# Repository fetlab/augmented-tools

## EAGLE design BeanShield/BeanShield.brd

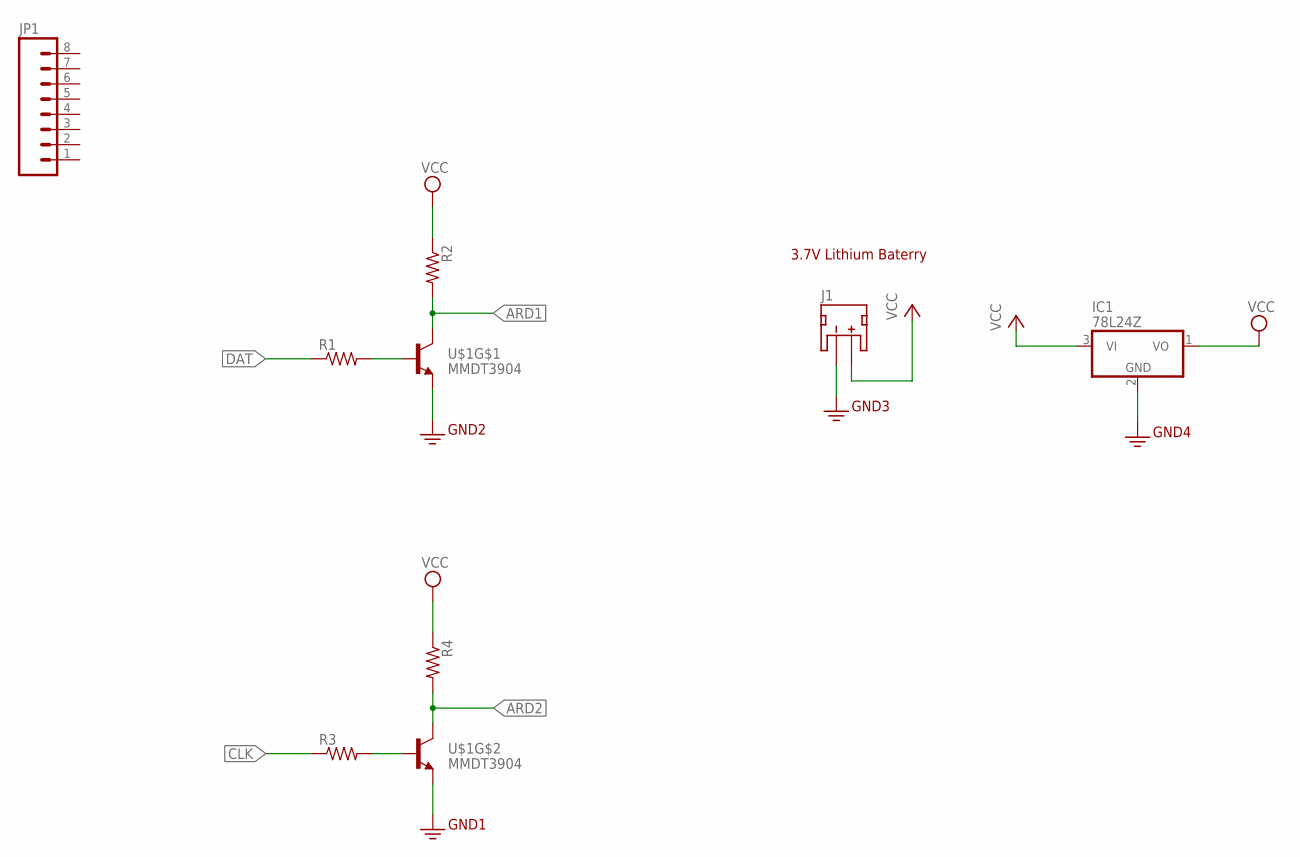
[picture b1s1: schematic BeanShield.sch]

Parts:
IC1: 78L24Z; TO92
J1: JST_2MM_MALE; JST-2-SMD
JP1: M08; 1X08_ROUND
R1, R2, R3, R4: RESISTOR0402; 0402-RES
U$1: MMDT3904; SOT363

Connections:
3.3V: IC1.2 (GND), J1.1 (-), U$1.1 (E), U$1.4 (E)
ARD1: R2.2, U$1.6 (C)
ARD2: R4.2, U$1.3 (C)
CLK: R3.1
DAT: R1.1
unnamed: R1.2, U$1.2 (B)
unnamed: R3.2, U$1.5 (B)
VCC: IC1.1 (VO), IC1.3 (VI), J1.2 (+), R2.1, R4.1

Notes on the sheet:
3.7V Lithium Baterry

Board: 2 copper layers, 8 parts (0 on the bottom side), 6 nets, no tracks yet.

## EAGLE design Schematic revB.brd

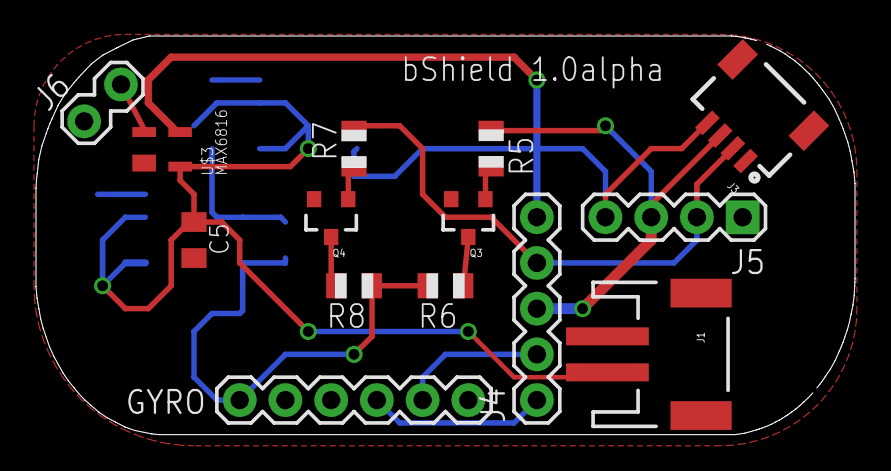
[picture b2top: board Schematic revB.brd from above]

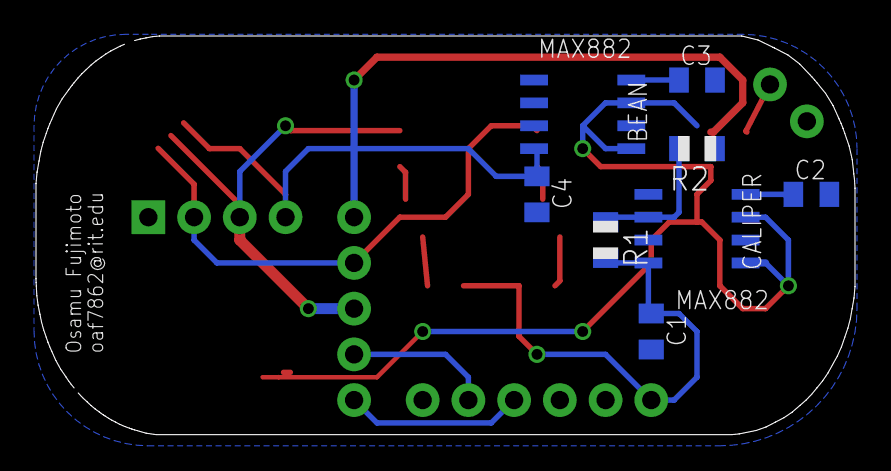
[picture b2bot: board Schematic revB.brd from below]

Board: 2 copper layers, 45.5 x 22.1 mm, 22 parts (8 on the bottom side), 17 nets.

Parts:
BEAN: MAX882; SOIC8
C1, C4: 2.2uF; C0805K
C2, C3, C5: 1uF; C0805K
CALIPER: MAX882; SOIC8
GYRO: 1X06
J1: JST-2-SMD
J3: 1X04-1MM-RA
J4: 1X05
J5: 1X04
J6: 1X02_LOCK
Q3, Q4: MMBT5088; SOT23-3
R1, R2, R5, R6, R7, R8: 10K; R0805
U$3: MAX6816; SOT143

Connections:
+3V3: C1.1, CALIPER.P$4, GYRO.1, R1.2, R6.2, R8.1
CLK: J3.3, J4.3, J5.3, R5.1
DB1: J4.5, U$3.P$3
G-CLK: GYRO.5, J4.2
G-SDA: GYRO.4, J4.1
GND: BEAN.P$2, BEAN.P$3, BEAN.P$6, C1.2, C2.2, C3.2, C4.2, C5.2, CALIPER.P$3, CALIPER.P$6, GYRO.3, J1.1, J3.1, J5.1, J6.1, Q3.2, Q4.2, R2.1, U$3.P$1
unnamed: Q3.1, R5.2
unnamed: Q3.3, R6.1
unnamed: Q4.1, R7.1
unnamed: Q4.3, R8.2
unnamed: BEAN.P$8, C3.1
unnamed: C2.1, CALIPER.P$8
unnamed: CALIPER.P$2, R1.1, R2.2
unnamed: J6.2, U$3.P$2
SDA: J3.2, J4.4, J5.2, R7.2
V+: BEAN.P$4, C4.1, J3.4, J5.4
VIN: BEAN.P$5, BEAN.P$7, C5.1, CALIPER.P$5, CALIPER.P$7, J1.2, U$3.P$4

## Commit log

2015-12-18 BeanShield empty project
2015-12-19 data/clock input
2015-12-19 added logotype to frame
2016-01-07 added sample code for orientation
2016-01-07 added documentation
2016-02-02 Create CaliperRenderer.js
    JS file that renders a cylinder with values given on page load.
2016-02-02 Create CaliperRender.html
    HTML file which imports all JS files required for CaliperRenderer
2016-04-14 schematic for revB of the Board

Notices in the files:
parts and their libraries:
SparkFun-DiscreteSemi: Licensing: Creative Commons ShareAlike 4.0 International - https://creativecommons.org/licenses/by-sa/4.0
